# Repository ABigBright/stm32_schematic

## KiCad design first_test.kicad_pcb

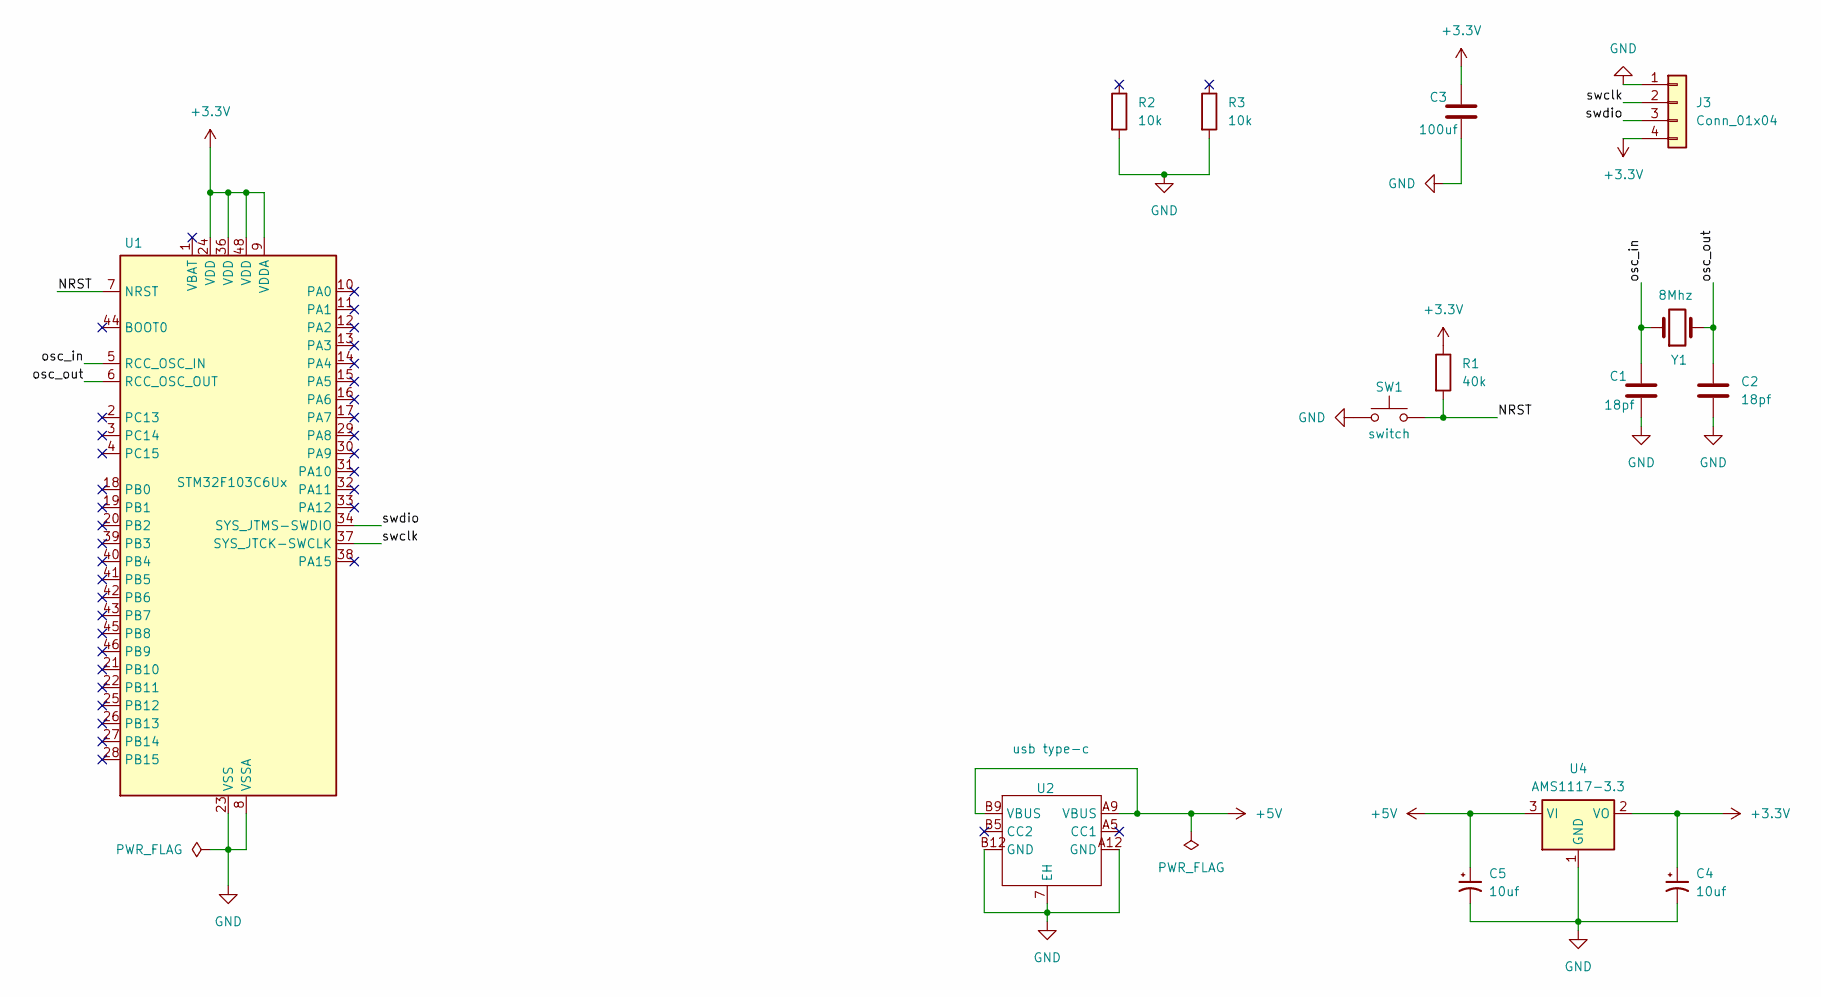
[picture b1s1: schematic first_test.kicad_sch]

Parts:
C1, C2: 18pf; C_0603_1608Metric
C3: 100uf; CP_Elec_8x10.5
C4, C5: 10uf; C_0603_1608Metric
J3: Conn_01x04; PinHeader_1x04_P2.54mm_Horizontal
R1: 40k; R_0603_1608Metric
R2, R3: 10k; R_0603_1608Metric
SW1: switch; SW_PUSH_6mm
U1: STM32F103C6Ux; LQFP-48-1EP_7x7mm_P0.5mm_EP3.6x3.6mm
U2: usb type-c; usb_c_6pin
U4: AMS1117-3.3; SOT-223-3_TabPin2
Y1: 8Mhz; Crystal_SMD_HC49-SD

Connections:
+3.3V: C3.1, C4.1, J3.4, R1.1, U1.9 (VDDA), U1.24 (VDD), U1.36 (VDD), U1.48 (VDD), U4.2 (VO)
+5V: C5.1, U2.A9 (VBUS), U2.B9 (VBUS), U4.3 (VI)
/NRST: R1.2, SW1.2, U1.7 (NRST)
/osc_in: C1.1, U1.5 (RCC_OSC_IN), Y1.1
/osc_out: C2.1, U1.6 (RCC_OSC_OUT), Y1.2
/swclk: J3.2, U1.37 (SYS_JTCK-SWCLK)
/swdio: J3.3, U1.34 (SYS_JTMS-SWDIO)
GND: C1.2, C2.2, C3.2, C4.2, C5.2, J3.1, R2.2, R3.2, SW1.1, U1.8 (VSSA), U1.23 (VSS), U1.35 (VSS), U1.47 (VSS), U1.49 (VSS), U2.7 (EH), U2.A12 (GND), U2.B12 (GND), U4.1 (GND)

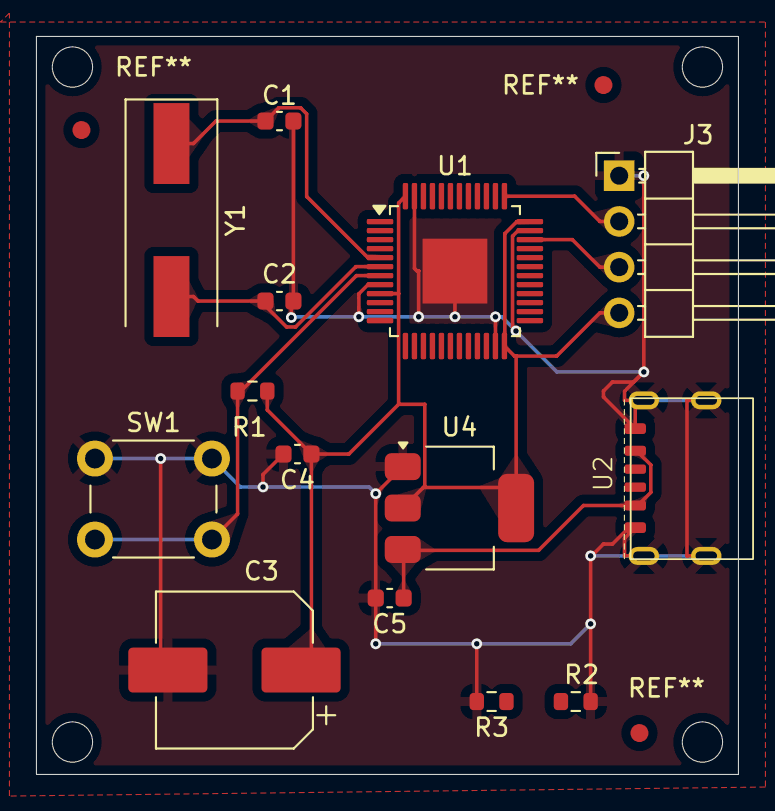
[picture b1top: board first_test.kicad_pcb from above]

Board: 2 copper layers, 39.0 x 41.0 mm, 14 parts (0 on the bottom side), 8 nets.

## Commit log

2025-01-09 init: just backup my stm32 kicad project, first commit
2025-01-12 feat: add customize symbol and footprint
2025-01-13 feat: remove unused file
2025-01-13 feat: add marker for smt
